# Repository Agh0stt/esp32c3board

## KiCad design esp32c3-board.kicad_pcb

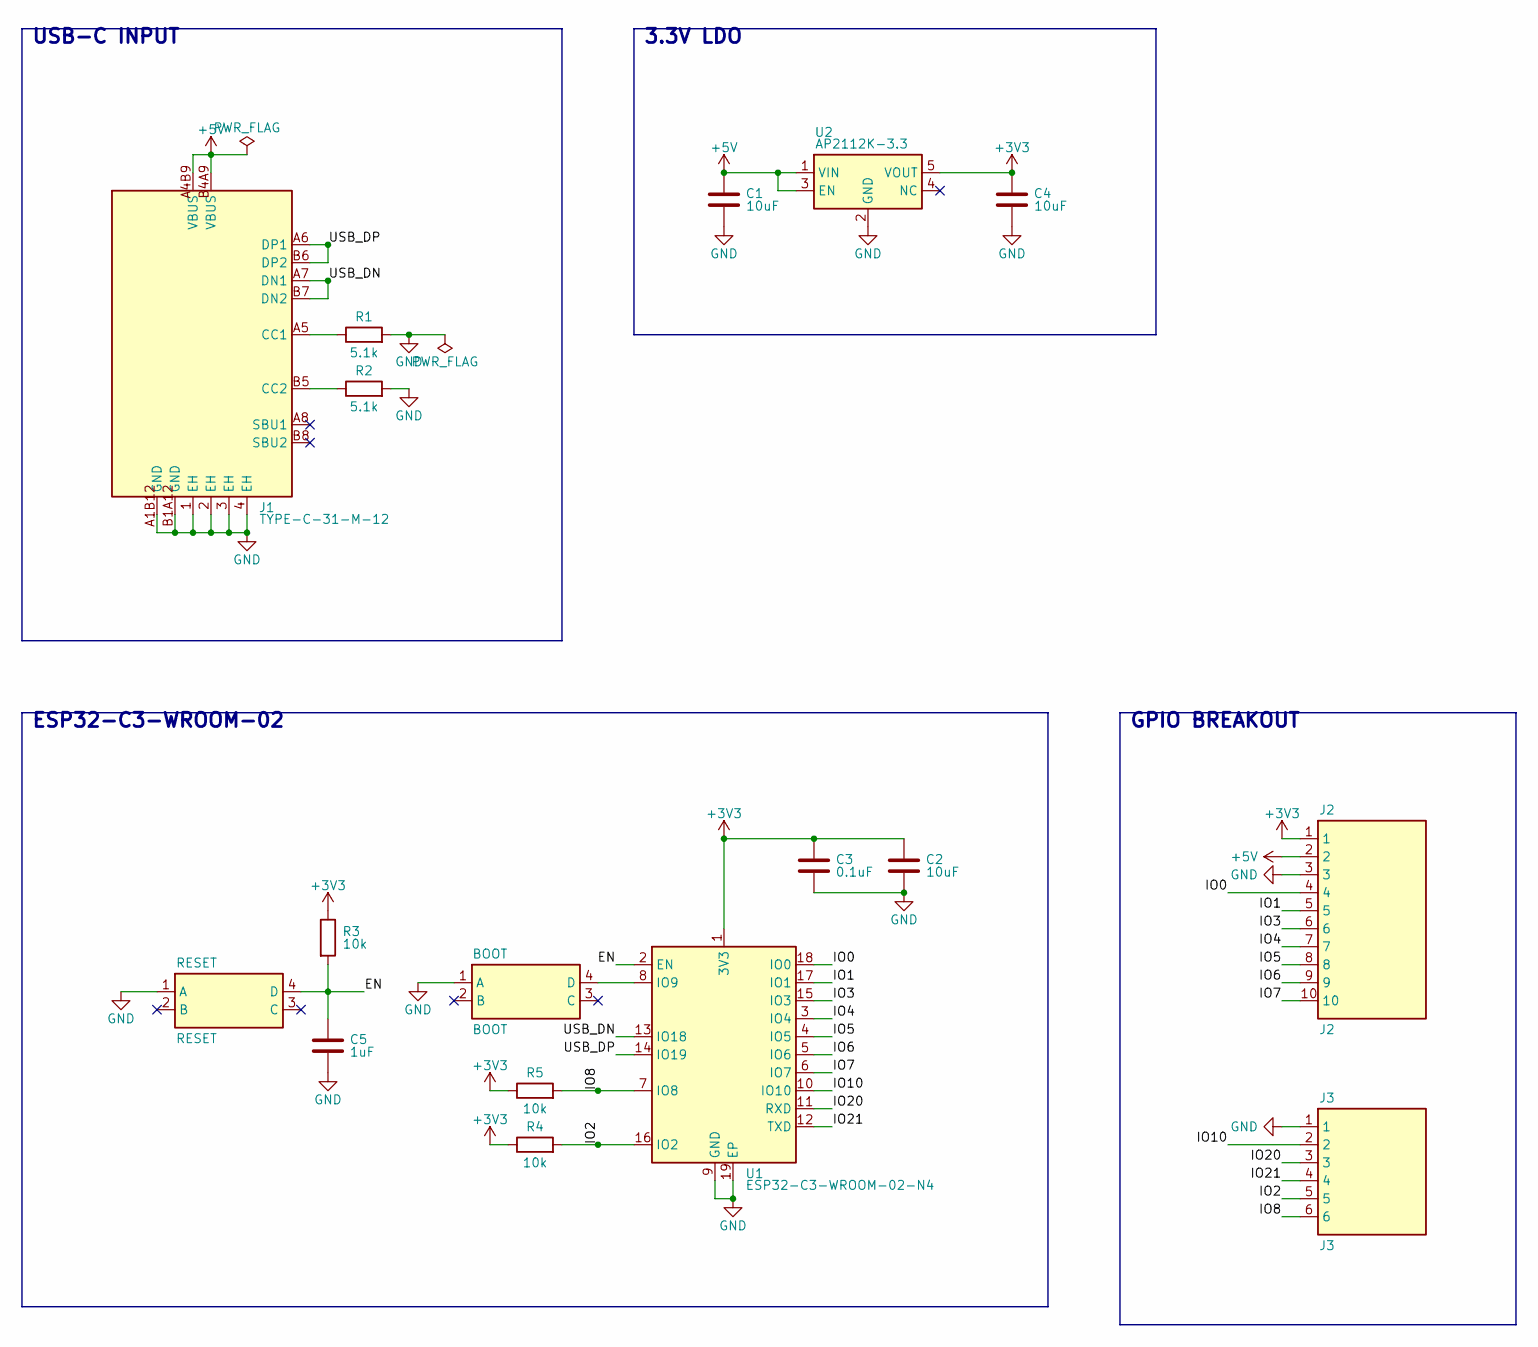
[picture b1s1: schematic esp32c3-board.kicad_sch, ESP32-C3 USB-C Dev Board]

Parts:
BOOT: BOOT; SW-SMD_4P-L5.1-W5.1-P3.70-LS6.5-TL_H1.5; MPN TS-1187A-B-A-B; LCSC C318884
C1, C2, C4: 10uF; C_0805_2012Metric; LCSC C15850
C3: 0.1uF; C_0603_1608Metric; LCSC C14663
C5: 1uF; C_0603_1608Metric; LCSC C15849
J1: TYPE-C-31-M-12; USB-C_SMD-TYPE-C-31-M-12_1; MPN TYPE-C-31-M-12; LCSC C165948
J2: J2; HDR-TH_10P-P2.54-V-M; MPN PZ254V-11-10P; LCSC C492409
J3: J3; HDR-TH_6P-P2.54-V-M; MPN PZ254V-11-06P; LCSC C492405
R1, R2: 5.1k; R_0603_1608Metric; LCSC C23186
R3, R4, R5: 10k; R_0603_1608Metric; LCSC C25804
RESET: RESET; SW-SMD_4P-L5.1-W5.1-P3.70-LS6.5-TL_H1.5; MPN TS-1187A-B-A-B; LCSC C318884
U1: ESP32-C3-WROOM-02-N4; BULETM-SMD_ESPRESSIF_ESP32-C3-WROOM-02-N4-4MB; MPN ESP32-C3-WROOM-02-N4; LCSC C2934560
U2: AP2112K-3.3; SOT-25-5_L2.9-W1.6-P0.95-LS2.8-BL; MPN AP2112K-3.3TRG1; LCSC C51118

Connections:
+3V3: C2.1, C3.1, C4.1, J2.1, R3.1, R4.1, R5.1, U1.1 (3V3), U2.5 (VOUT)
+5V: C1.1, J1.A4B9 (VBUS), J1.B4A9 (VBUS), J2.2, U2.1 (VIN), U2.3 (EN)
/EN: C5.1, R3.2, RESET.4 (D), U1.2 (EN)
/IO0: J2.4, U1.18 (IO0)
/IO1: J2.5, U1.17 (IO1)
/IO2: J3.5, R4.2, U1.16 (IO2)
/IO3: J2.6, U1.15 (IO3)
/IO4: J2.7, U1.3 (IO4)
/IO5: J2.8, U1.4 (IO5)
/IO6: J2.9, U1.5 (IO6)
/IO7: J2.10, U1.6 (IO7)
/IO8: J3.6, R5.2, U1.7 (IO8)
/IO10: J3.2, U1.10 (IO10)
/IO20: J3.3, U1.11 (RXD)
/IO21: J3.4, U1.12 (TXD)
/USB_DN: J1.A7 (DN1), J1.B7 (DN2), U1.13 (IO18)
/USB_DP: J1.A6 (DP1), J1.B6 (DP2), U1.14 (IO19)
GND: BOOT.1 (A), C1.2, C2.2, C3.2, C4.2, C5.2, J1.1 (EH), J1.2 (EH), J1.3 (EH), J1.4 (EH), J1.A1B12 (GND), J1.B1A12 (GND), J2.3, J3.1, R1.2, R2.2, RESET.1 (A), U1.9 (GND), U1.19 (EP), U2.2 (GND)
unnamed: BOOT.4 (D), U1.8 (IO9)
unnamed: J1.A5 (CC1), R1.1
unnamed: J1.B5 (CC2), R2.1

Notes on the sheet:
3.3V LDO
GPIO BREAKOUT
USB-C INPUT
ESP32-C3-WROOM-02

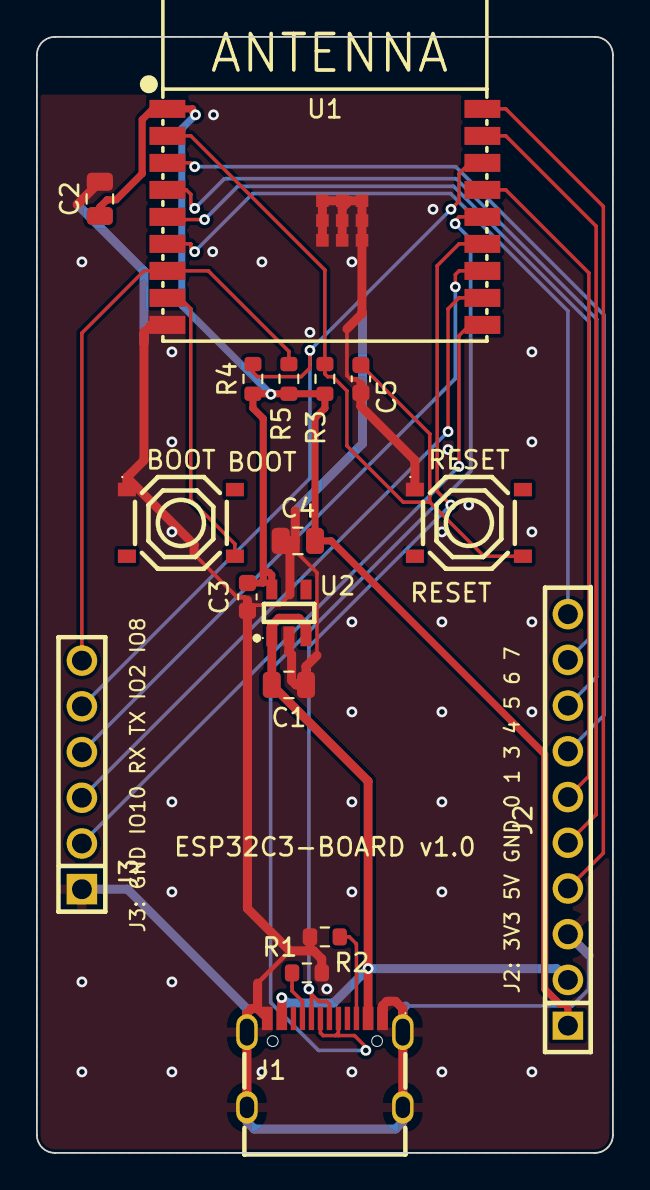
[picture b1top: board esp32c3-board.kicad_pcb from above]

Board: 2 copper layers, 32.0 x 62.0 mm, 17 parts (0 on the bottom side), 21 nets.
